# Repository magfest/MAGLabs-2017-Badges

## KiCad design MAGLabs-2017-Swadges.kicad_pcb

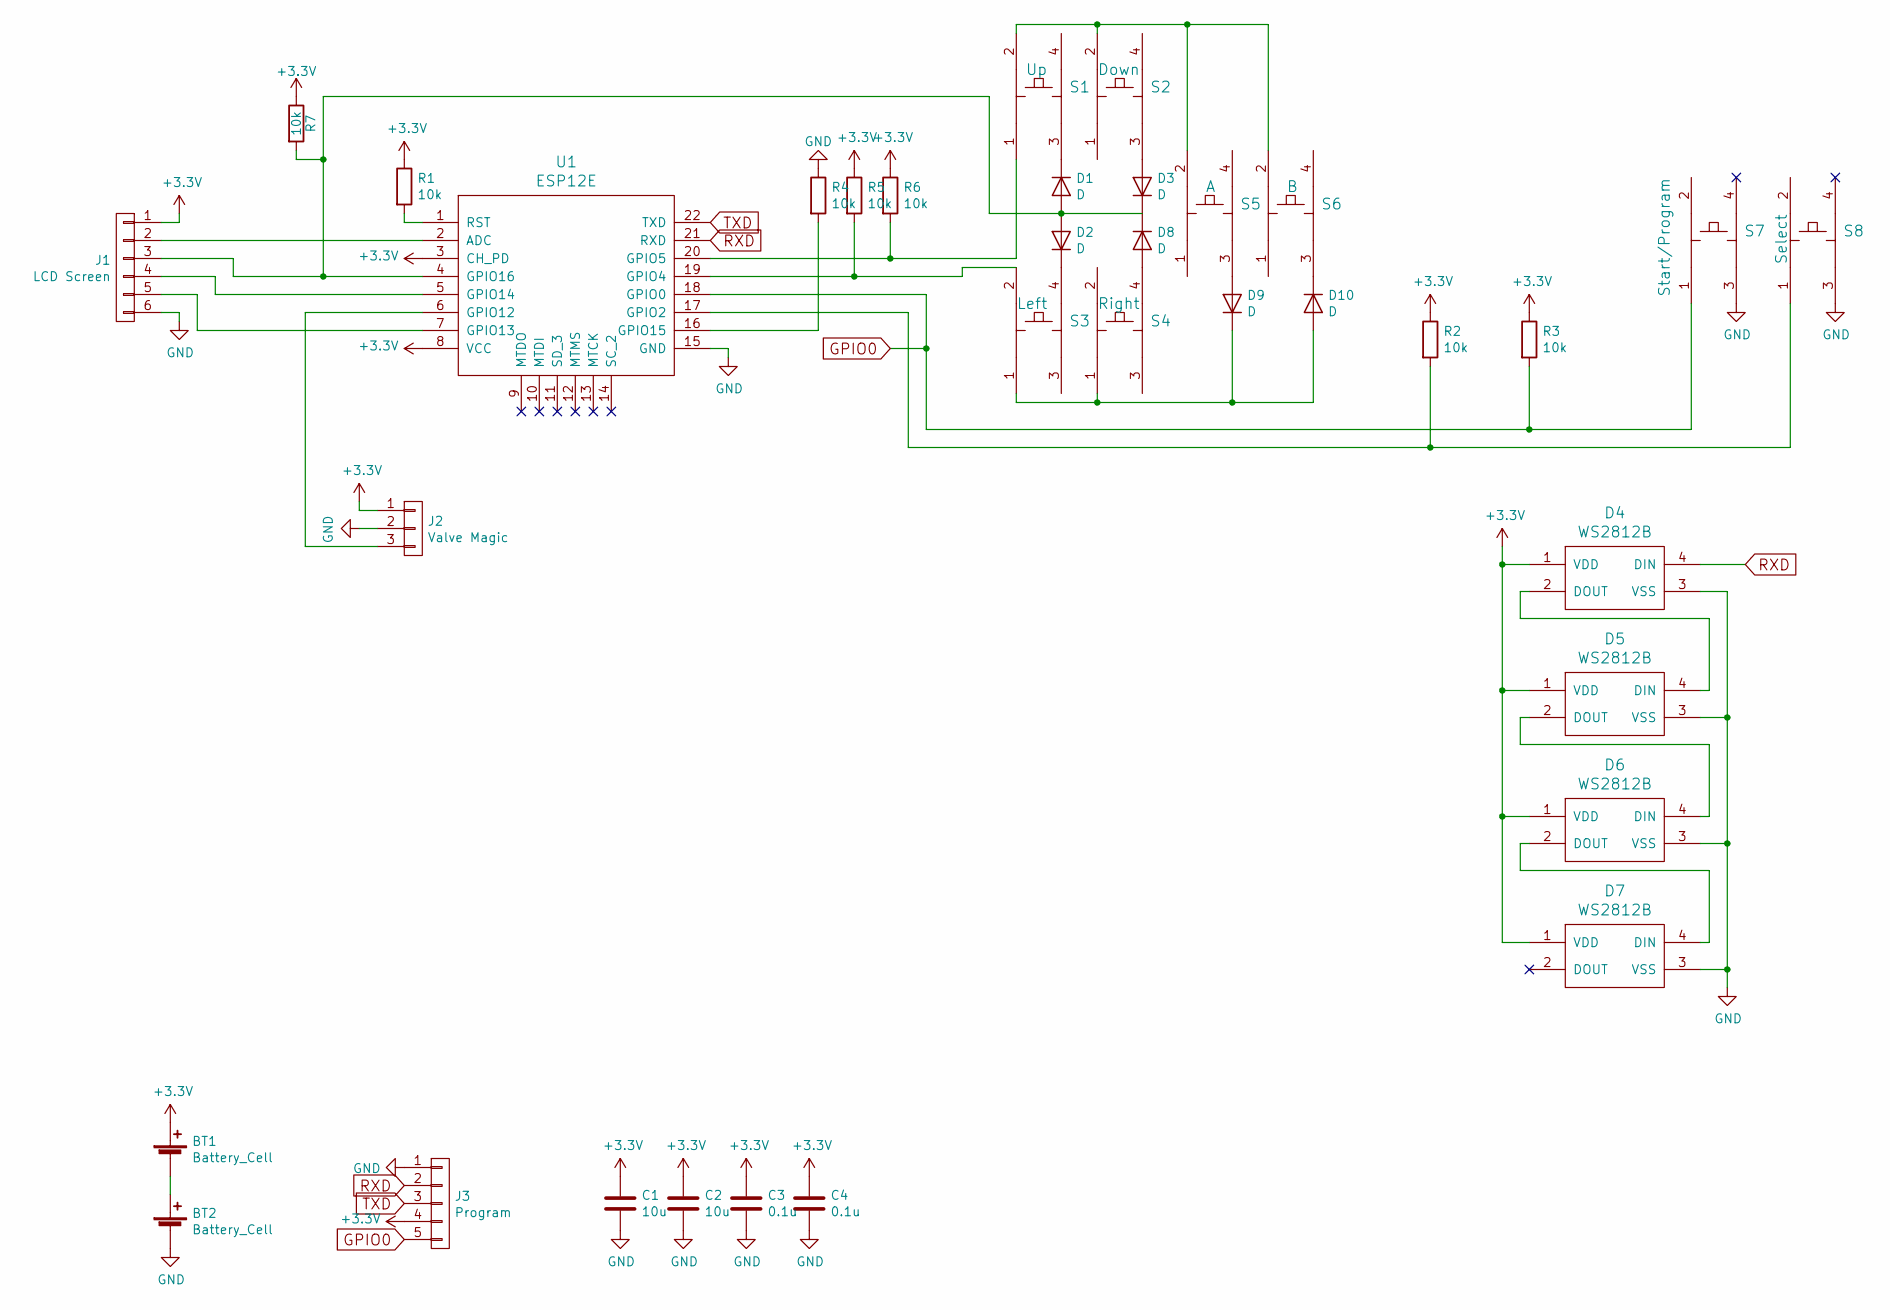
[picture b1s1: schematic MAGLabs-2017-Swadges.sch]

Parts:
BT1, BT2: Battery_Cell; Elecrow-ThroughHole-AA-Battery
C1, C2: 10u; C_0603
C3, C4: 0.1u; C_0603
D1, D2, D3, D8, D9, D10: D; D_SOD-323
D4, D5, D6, D7: WS2812B
J1: LCD Screen; Pin_Header_Straight_1x06_Pitch2.54mm
J2: Valve Magic; VALVE_CHICKLET_8_1
J3: Program; Pin_Header_Straight_1x05_Pitch2.54mm
R1, R2, R3, R4, R5, R6, R7: 10k; R_0603
S1: Up; PTS645
S2: Down; PTS645
S3: Left; PTS645
S4: Right; PTS645
S5: A; PTS645
S6: B; PTS645
S7: Start/Program; PTS645
S8: Select; PTS645
U1: ESP12E

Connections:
+3V3: BT1.1 (+), C1.1, C2.1, C3.1, C4.1, D4.1 (VDD), D5.1 (VDD), D6.1 (VDD), D7.1 (VDD), J1.1, J2.1, J3.4, R1.1, R2.1, R3.1, R5.1, R6.1, R7.1, U1.3 (CH_PD), U1.8 (VCC)
GND: BT2.2 (-), C1.2, C2.2, C3.2, C4.2, D4.3 (VSS), D5.3 (VSS), D6.3 (VSS), D7.3 (VSS), J1.6, J2.2, J3.1, R4.1, S7.3, S8.3, U1.15 (GND)
GPIO0: J3.5, R3.2, S7.1, U1.18 (GPIO0)
unnamed: BT1.2 (-), BT2.1 (+)
unnamed: D1.1 (K), S1.3
unnamed: D1.2 (A), D2.2 (A), D3.1 (K), D8.1 (K), J1.3, R7.2, U1.4 (GPIO16)
unnamed: D2.1 (K), S3.4
unnamed: D3.2 (A), S2.3
unnamed: D4.2 (DOUT), D5.4 (DIN)
unnamed: D5.2 (DOUT), D6.4 (DIN)
unnamed: D6.2 (DOUT), D7.4 (DIN)
unnamed: D8.2 (A), S4.4
unnamed: D9.2 (A), S5.3
unnamed: D10.1 (K), S6.3
unnamed: D9.1 (K), D10.2 (A), S3.1, S4.1
unnamed: J1.2, U1.2 (ADC)
unnamed: J1.4, U1.5 (GPIO14)
unnamed: J1.5, U1.7 (GPIO13)
unnamed: J2.3, U1.6 (GPIO12)
unnamed: R1.2, U1.1 (RST)
unnamed: R2.2, S8.1, U1.17 (GPIO2)
unnamed: R4.2, U1.16 (GPIO15)
unnamed: R5.2, S3.2, U1.19 (GPIO4)
unnamed: R6.2, S1.1, U1.20 (GPIO5)
unnamed: S1.2, S2.2, S5.2, S6.2
RXD: D4.4 (DIN), J3.2, U1.21 (RXD)
TXD: J3.3, U1.22 (TXD)

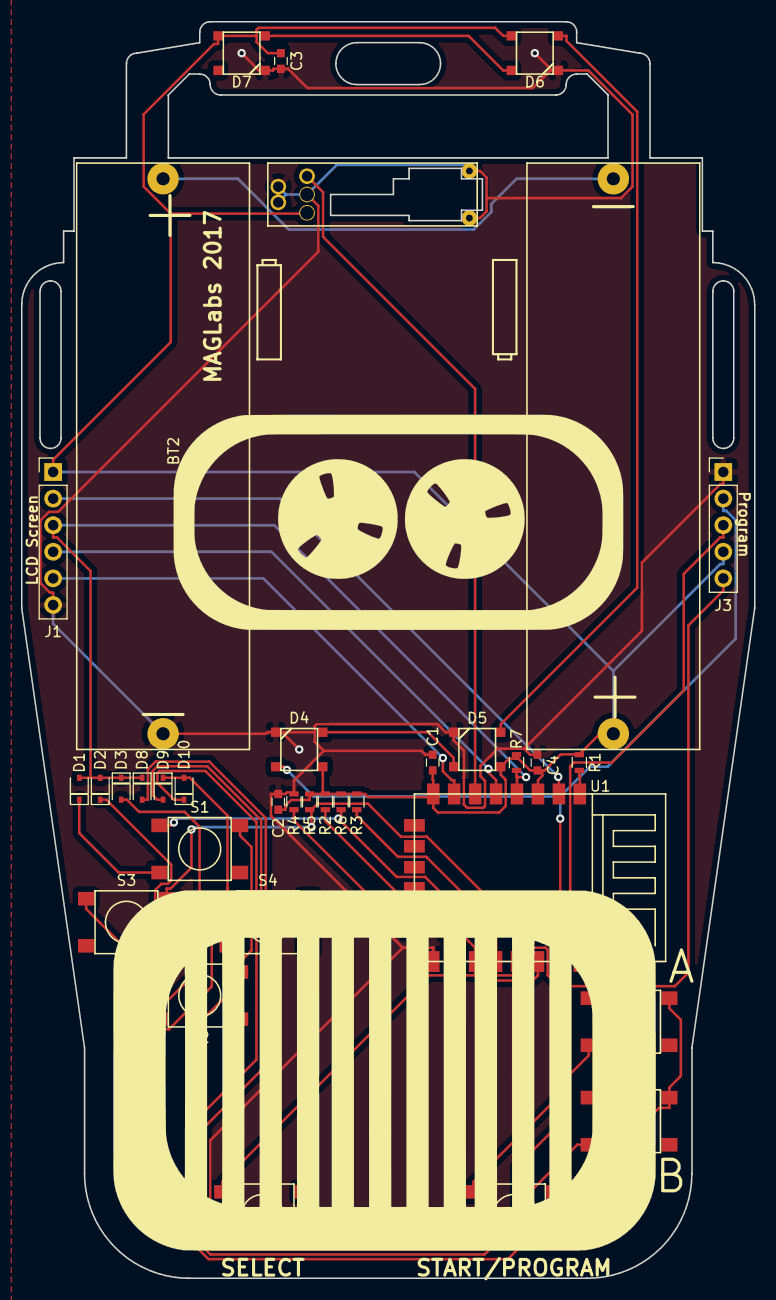
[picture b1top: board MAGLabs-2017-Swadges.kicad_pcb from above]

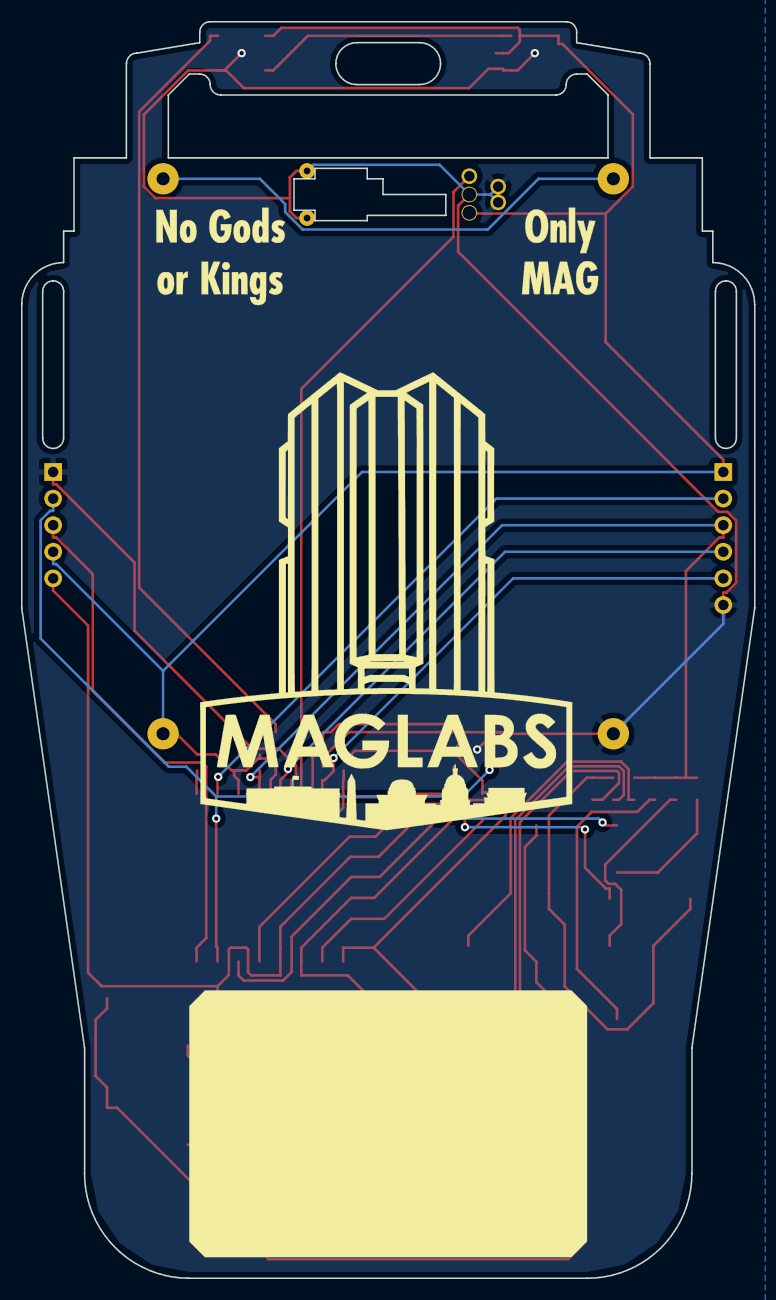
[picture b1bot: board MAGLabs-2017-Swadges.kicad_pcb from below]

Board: 2 copper layers, 70.0 x 120.0 mm, 37 parts (2 on the bottom side), 27 nets.

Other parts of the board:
G1: LOGO; maglabs-backv2
G2: LOGO; maglabs-frontv2

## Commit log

2017-07-20 Update design with Valve
2017-07-20 Now with pullups
2017-07-20 All fabrication outputs should be ready
2017-07-21 remove outputs
2017-07-21 Update outputs
2017-07-21 Update Swadges design
2017-07-21 Cleanup outputs
2017-07-21 oops fixed gerbers
2017-07-21 Update design
2017-07-21 Fixed diodes
2017-07-21 Added button labels
2017-07-22 Removed autosave
2017-07-31 Updated schematic
2017-08-01 Pre route
2017-08-01 Should be good?
2017-08-01 Adjusted vive sensor, moved art to silkscreen
2017-08-01 Citizen
2017-08-01 Added zip
2017-08-01 All prod files
2017-08-04 Add citizen2 + update outputs
2017-08-17 Add esp82xx firmware
2017-08-17 Add the rest of the esp82xx firmware setup
2017-08-17 Update! With primitive lighthouse support
2017-08-19 Update vive_help switch to dev branch
2017-08-19 Update to current version of swadge!
2017-08-19 Added button readout
2017-08-20 Bump
2017-08-20 Clearer button stuff
2017-08-20 Fix button display ordering
2017-08-20 Remove prototype ifdef
2017-08-22 Buttons except L, R, B working
2017-08-22 Rearrange button readouts to fix all but R
2017-08-31 At-Fest
2017-08-31 SHIPPIT
2017-09-01 Reworking code
2017-09-01 Trying to send packets
2017-09-01 No longer sending or receiving packets
2017-09-01 Feature parity
2017-09-01 First set of badge ids
2017-09-01 Accepts and sends charlesnet
2017-09-02 Update - don't override speeds.
2017-09-02 Update with new version number
2017-09-02 Update with thing saying reason for crash
2017-09-02 Update to get rid of GPIO0
2017-09-02 remove extra printf
2017-09-02 Merged
2017-09-02 remove unused flag
2017-09-02 Update with correct LED usage.
2017-09-02 Update with new firmware
2017-09-02 Added netflash.py
2017-09-02 Starting on a display
2017-09-02 Actually display text on supporter badges
2017-09-02 Update to accept OLED commands
2017-09-02 Update LED text
2017-09-03 bump version rev
